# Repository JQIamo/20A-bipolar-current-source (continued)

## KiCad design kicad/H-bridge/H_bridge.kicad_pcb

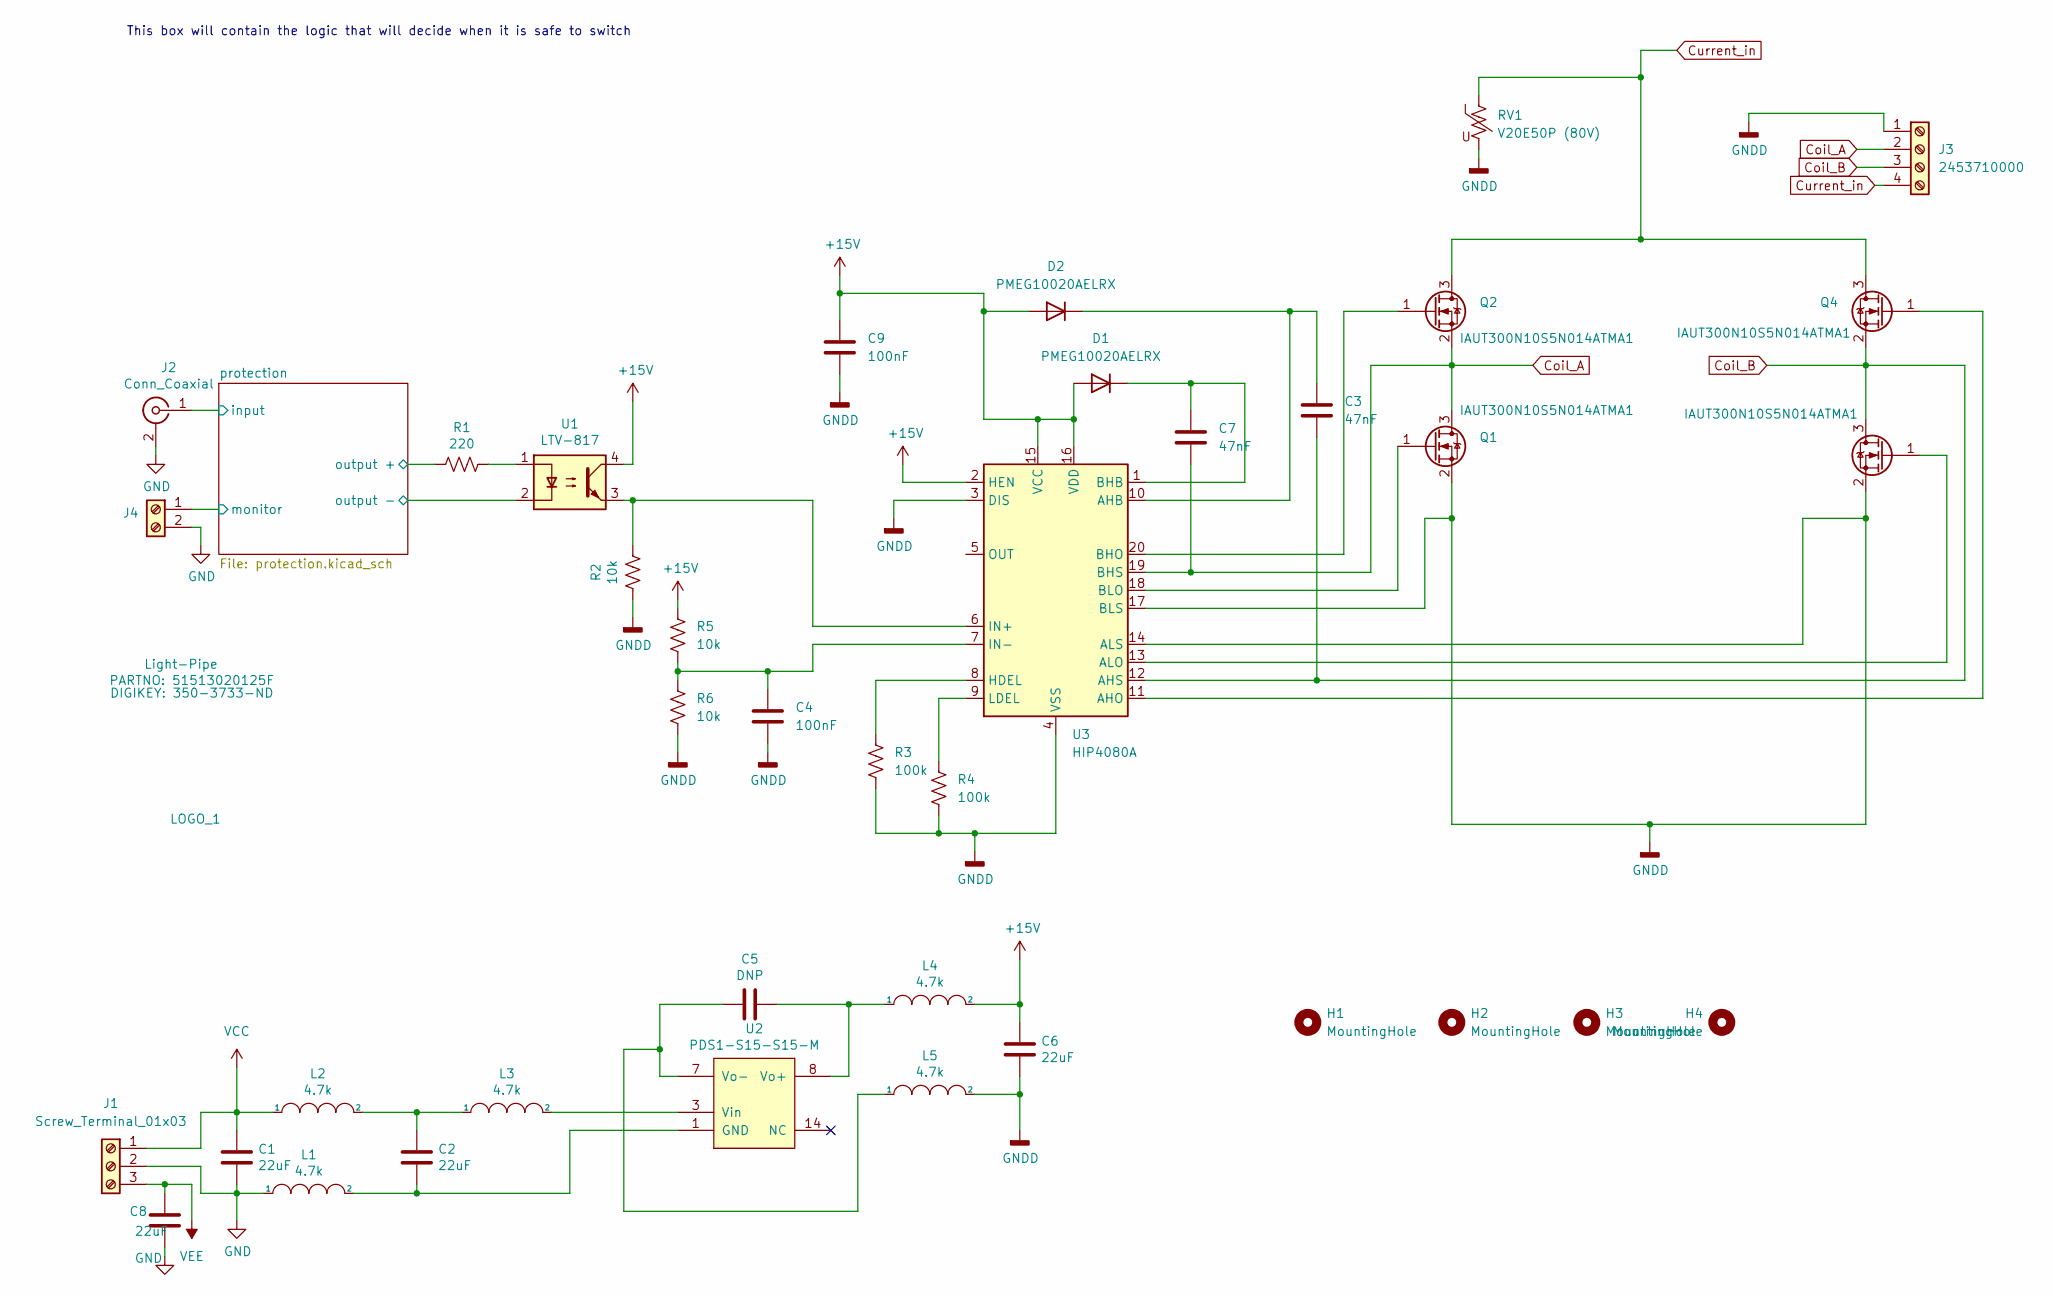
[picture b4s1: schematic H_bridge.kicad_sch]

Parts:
BOM1: Light-Pipe; PARTNO 51513020125F; DIGIKEY 350-3733-ND
C1, C2, C6, C8: 22uF; C_0805_2012Metric; PARTNO C2012X5R1V226M125AC; DIGIKEY 445-14428-1-ND
C3, C7: 47nF; C_0805_2012Metric; PARTNO C0805C473K2RECAUTO; DIGIKEY 399-C0805C473K2RECAUTOCT-ND
C4, C9: 100nF; C_0805_2012Metric; PARTNO CC0805KRX7R9BB104; DIGIKEY 311-1140-1-ND
C5: DNP; C_0805_2012Metric
D1, D2: PMEG10020AELRX; Nexperia_CFP3_SOD-123W; PARTNO PMEG10020AELRX; DIGIKEY 1727-2283-1-ND
H1, H2, H3, H4: MountingHole; MountingHole_3.5mm
J1: Screw_Terminal_01x03; TerminalBlock_4Ucon_1x03_P3.50mm_Horizontal; PARTNO 1984620; DIGIKEY 277-1722-ND
J2: Conn_Coaxial; BNC_Socket_TYCO-AMP; PARTNO 5227161-7; DIGIKEY A32260-ND
J3: 2453710000; CONN_2453710000; PARTNO 2453710000; DIGIKEY 2453710000-ND
J4: Screw_Terminal_01x02; TerminalBlock_4Ucon_1x02_P3.50mm_Horizontal; PARTNO 1984617; DIGIKEY 277-1721-ND
L1, L2, L3, L4, L5: 4.7k; L_0805; PARTNO BLM21HE472SN1L; DIGIKEY 490-BLM21HE472SN1LCT-ND
LOGO_1: JQI-Logo
Q1, Q2, Q3, Q4: IAUT300N10S5N014ATMA1; Infineon_PG-HSOF-8-1_ThermalVias; PARTNO IAUT300N10S5N014ATMA1; DIGIKEY 448-IAUT300N10S5N014ATMA1CT-ND
R1: 220; R_0805; PARTNO CRGCQ0805F220R; DIGIKEY A129741CT-ND
R2, R5, R6: 10k; R_0805_2012Metric; PARTNO CRGCQ0805F10K; DIGIKEY A129761CT-ND
R3, R4: 100k; R_0805_2012Metric; PARTNO CRG0805F100K; DIGIKEY A106052CT-ND
RV1: V20E50P (80V); RV_Disc_D15.5mm_W7.5mm_P7.5mm; PARTNO V20E50P; DIGIKEY F6901-ND
U1: LTV-817; DIP-4_W10.16mm_LongPads; PARTNO LTV-817; DIGIKEY 160-1366-5-ND
U2: PDS1-S15-S15-M; DCDC-Conv_muRata_NXE2SxxxxMC; PARTNO PDS1-S15-S15-M; DIGIKEY 102-4546-ND
U3: HIP4080A; SO-20_12.8x7.5mm_P1.27mm; PARTNO HIP4080AIBZT; DIGIKEY HIP4080AIBZTCT-ND

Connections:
+15V: C6.2, C9.1, D1.2 (A), D2.2 (A), L4.2, R5.1, U1.4, U3.2 (HEN), U3.15 (VCC), U3.16 (VDD)
/protection/input: J2.1 (In); also elsewhere on the board
/protection/monitor: J4.1; also elsewhere on the board
/protection/output +: R1.2; also elsewhere on the board
/protection/output -: U1.2; also elsewhere on the board
Coil_A: C7.2, J3.2, Q1.3 (D), Q2.2 (S), U3.19 (BHS)
Coil_B: C3.2, J3.3, Q3.3 (D), Q4.2 (S), U3.12 (AHS)
Current_in: J3.4, Q2.3 (D), Q4.3 (D), RV1.1
GND: C1.2, C8.2, J1.2, J2.2 (Ext), J4.2, L1.1; also elsewhere on the board
GNDD: C4.2, C6.1, C9.2, J3.1, L5.2, Q1.2 (S), Q3.2 (S), R2.2, R3.2, R4.2, R6.2, RV1.2, U3.3 (DIS), U3.4 (VSS), U3.14 (ALS), U3.17 (BLS)
unnamed: C2.1, L2.2, L3.1
unnamed: C7.1, D1.1 (K), U3.1 (BHB)
unnamed: C3.1, D2.1 (K), U3.10 (AHB)
unnamed: Q1.1 (G), U3.18 (BLO)
unnamed: Q2.1 (G), U3.20 (BHO)
unnamed: Q3.1 (G), U3.13 (ALO)
unnamed: Q4.1 (G), U3.11 (AHO)
unnamed: R1.1, U1.1
unnamed: C2.2, L1.2, U2.1 (GND)
unnamed: L3.2, U2.3 (Vin)
unnamed: C5.1, L4.1, U2.8 (Vo+)
unnamed: C5.2, L5.1, U2.7 (Vo-)
unnamed: R3.1, U3.8 (HDEL)
unnamed: R2.1, U1.3, U3.6 (IN+)
unnamed: C4.1, R5.2, R6.1, U3.7 (IN-)
unnamed: R4.1, U3.9 (LDEL)
VCC: C1.1, J1.1, L2.1; also elsewhere on the board
VEE: C8.1, J1.3; also elsewhere on the board

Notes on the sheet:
This box will contain the logic that will decide when it is safe to switch

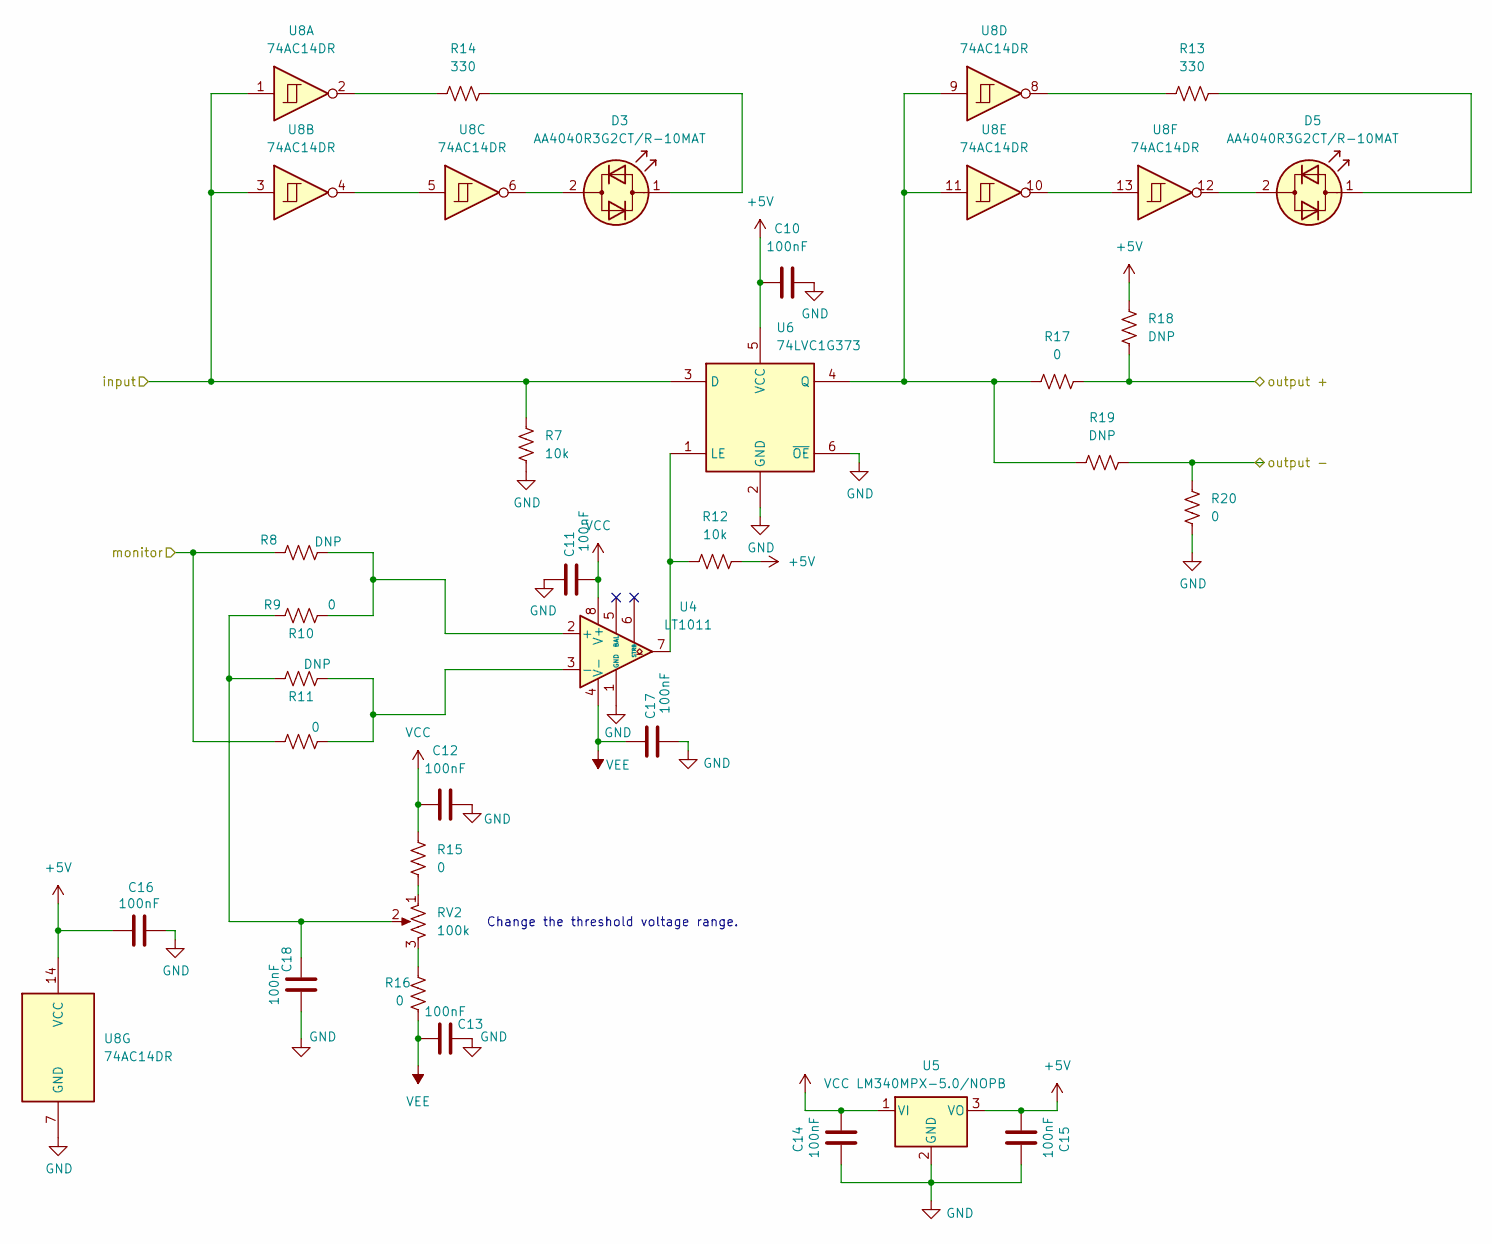
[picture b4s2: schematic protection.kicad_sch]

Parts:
C10, C11, C12, C13, C14, C15, C16, C17, C18: 100nF; C_0805_2012Metric; PARTNO CC0805KRX7R9BB104; DIGIKEY 311-1140-1-ND
D3, D5: AA4040R3G2CT/R-10MAT; LED_boomerang; PARTNO AA4040R3G2CT/R-10MAT; DIGIKEY 754-AA4040R3G2CT/R-10MATCT-ND
R7, R12: 10k; R_0805_2012Metric; PARTNO CRGCQ0805F10K; DIGIKEY A129761CT-ND
R8, R10, R18, R19: DNP; R_0805_2012Metric
R9, R11, R15, R16, R17, R20: 0; R_0805_2012Metric; PARTNO CRG0805ZR; DIGIKEY A106066CT-ND
R13, R14: 330; R_0805_2012Metric; PARTNO CRGCQ0805F330R; DIGIKEY A129743CT-ND
RV2: 100k; Potentiometer_Bourns_3266Y_Vertical; PARTNO 3266Y-1-104LF; DIGIKEY 3266Y-1-104LF-ND
U4: LT1011; SO-8_3.9x4.9mm_P1.27mm; PARTNO LT1011CS8#PBF; DIGIKEY LT1011CS8#PBF-ND
U5: LM340MPX-5.0/NOPB; SOT-223-3_TabPin2; PARTNO LM340MPX-5.0/NOPB; DIGIKEY LM340MPX-5.0/NOPBCT-ND
U6: 74LVC1G373; SOT-363_SC-70-6; PARTNO SN74LVC1G373DCKR; DIGIKEY 296-18775-1-ND
U8: 74AC14DR; SOIC-14_3.9x8.7mm_P1.27mm; PARTNO SN74AC14DR; DIGIKEY 296-4300-1-ND

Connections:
+5V: C10.1, C15.2, C16.2, R12.2, R18.2, U5.3 (VO), U6.5 (VCC), U8.14 (VCC)
/protection/input: R7.1, U6.3 (D), U8.1, U8.3; also elsewhere on the board
/protection/monitor: R8.1, R11.1; also elsewhere on the board
/protection/output +: R17.2, R18.1; also elsewhere on the board
/protection/output -: R19.1, R20.2; also elsewhere on the board
GND: C10.2, C11.2, C12.2, C13.2, C14.1, C15.1, C16.1, C17.1, C18.1, R7.2, R20.1, U4.1 (GND), U5.2 (GND), U6.2 (GND), U6.6 (~OE), U8.7 (GND); also elsewhere on the board
unnamed: C18.2, R9.1, R10.1, RV2.2
unnamed: D3.2 (AK), U8.6
unnamed: D3.1 (KA), R14.2
unnamed: D5.2 (AK), U8.12
unnamed: D5.1 (KA), R13.2
unnamed: R13.1, U8.8
unnamed: R14.1, U8.2
unnamed: R15.1, RV2.1
unnamed: R16.2, RV2.3
unnamed: R8.2, R9.2, U4.2 (+)
unnamed: R10.2, R11.2, U4.3 (-)
unnamed: R12.1, U4.7, U6.1 (LE)
unnamed: R17.1, R19.2, U6.4 (Q), U8.9, U8.11
unnamed: U8.4, U8.5
unnamed: U8.10, U8.13
VCC: C11.1, C12.1, C14.2, R15.2, U4.8 (V+), U5.1 (VI); also elsewhere on the board
VEE: C13.1, C17.2, R16.1, U4.4 (V-); also elsewhere on the board

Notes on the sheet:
Change the threshold voltage range.

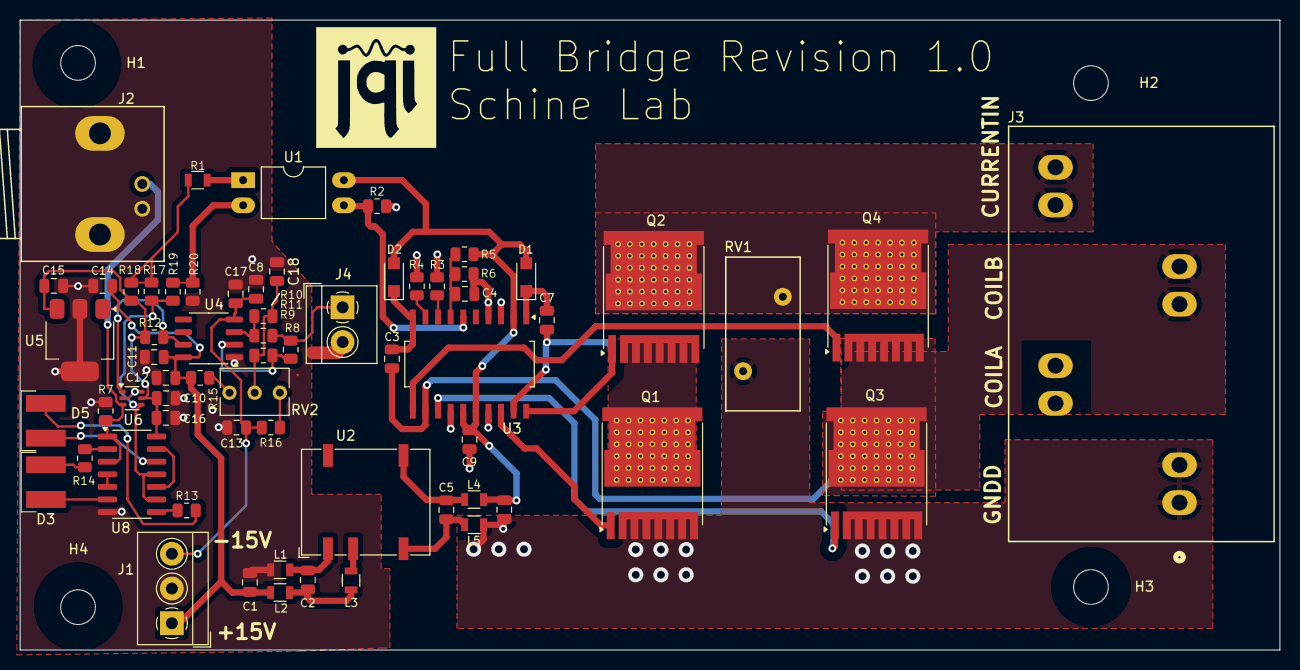
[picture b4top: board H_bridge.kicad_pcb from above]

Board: 2 copper layers, 127.0 x 63.5 mm, 69 parts (0 on the bottom side), 44 nets.

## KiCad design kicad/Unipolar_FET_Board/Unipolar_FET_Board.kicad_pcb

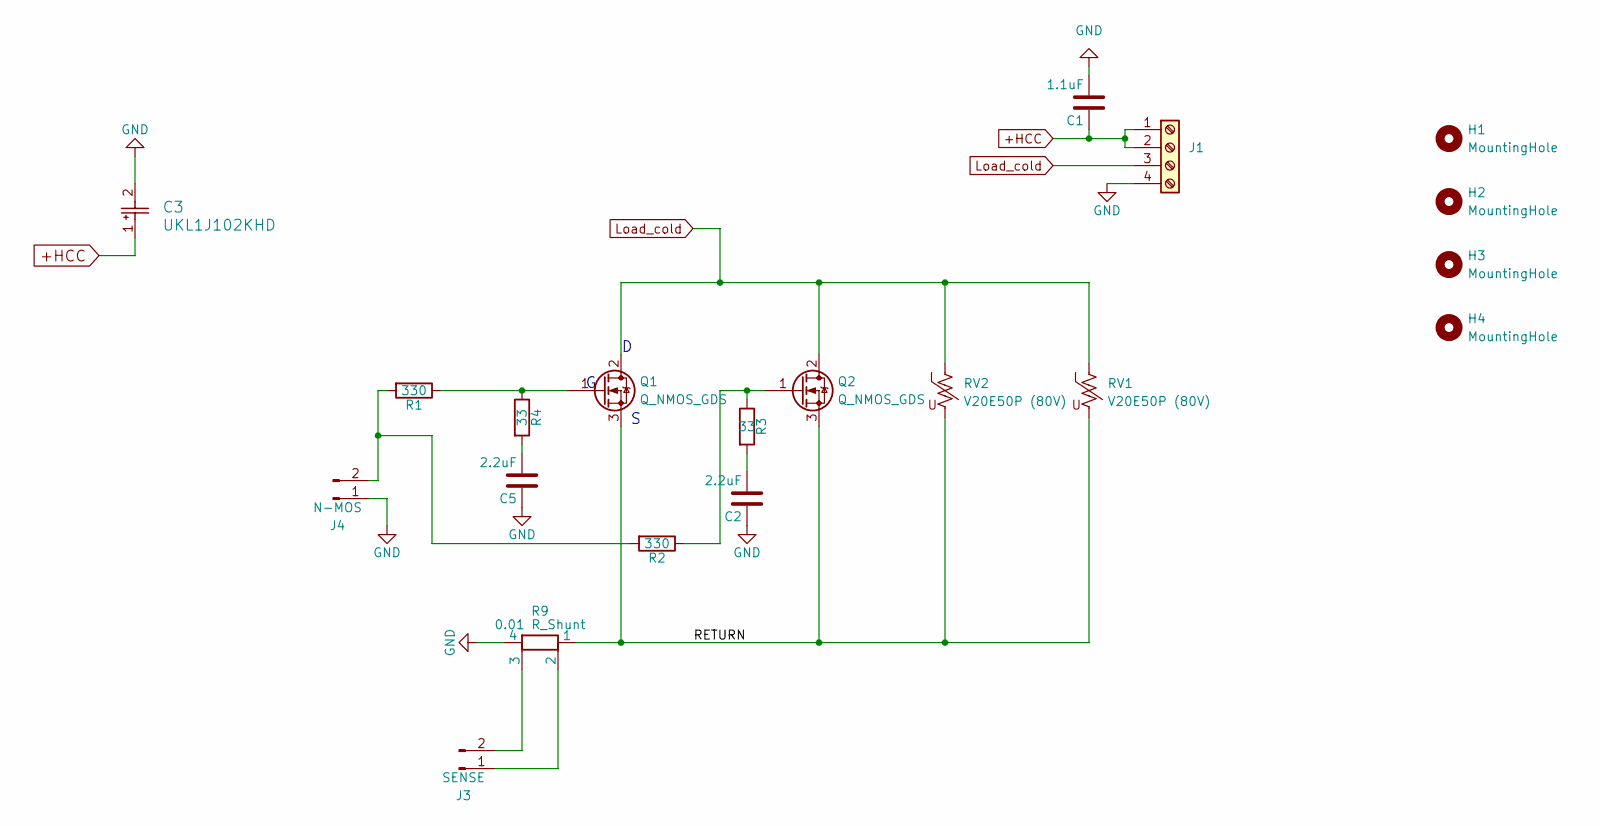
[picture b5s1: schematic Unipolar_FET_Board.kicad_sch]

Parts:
C1: 1.1uF; C_0603_1608Metric; MPN C0603C104J5RACAUTO; DIGIKEY PARTNO 399-6853-1-ND
C2, C5: 2.2uF; C_0603_1608Metric; MPN C0603C104J5RACAUTO; DIGIKEY PARTNO 399-6853-1-ND
C3: UKL1J102KHD; CP_Radial_D18.0mm_P7.50mm; PARTNO UKL1J102KHD; DIGIKEY 493-16867-ND
H1, H2, H3, H4: MountingHole; MountingHole_4mm
J1: Screw_Terminal_01x04; CONN_2453710000; PARTNO 2453710000; DIGIKEY 2453710000-ND
J3: SENSE; PinHeader_1x02_P2.54mm_Vertical
J4: N-MOS; PinHeader_1x02_P2.54mm_Vertical
Q1, Q2: Q_NMOS_GDS; PowerMOS; PARTNO IXFN520N075T2; DIGIKEY IXFN520N075T2-ND
R1, R2: 330; R_0603_1608Metric_Pad0.98x0.95mm_HandSolder; DIGIKEY PARTNO P20.00BYCT-ND
R3, R4: 33; R_0603_1608Metric_Pad0.98x0.95mm_HandSolder; DIGIKEY PARTNO P20.00BYCT-ND
R9: 0.01 R_Shunt; SIP-4-ShuntResistor-Riedon; PARTNO PCS-0R01D1; DIGIKEY 696-PCS-0R01D1-ND
RV1, RV2: V20E50P (80V); RV_Disc_D15.5mm_W7.5mm_P7.5mm; PARTNO V20E50P; DIGIKEY F6901-ND

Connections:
+HCC: C1.1, C3.1, J1.1, J1.2
/RETURN: Q1.3 (S), Q2.3 (S), R9.1, RV1.2, RV2.2
GND: C1.2, C2.1, C3.2, C5.1, J1.4, J4.1, R9.4
Load_cold: J1.3, Q1.2 (D), Q2.2 (D), RV1.1, RV2.1
unnamed: C2.2, R3.2
unnamed: C5.2, R4.2
unnamed: J3.1, R9.2
unnamed: J3.2, R9.3
unnamed: J4.2, R1.2, R2.2
unnamed: Q1.1 (G), R1.1, R4.1
unnamed: Q2.1 (G), R2.1, R3.1

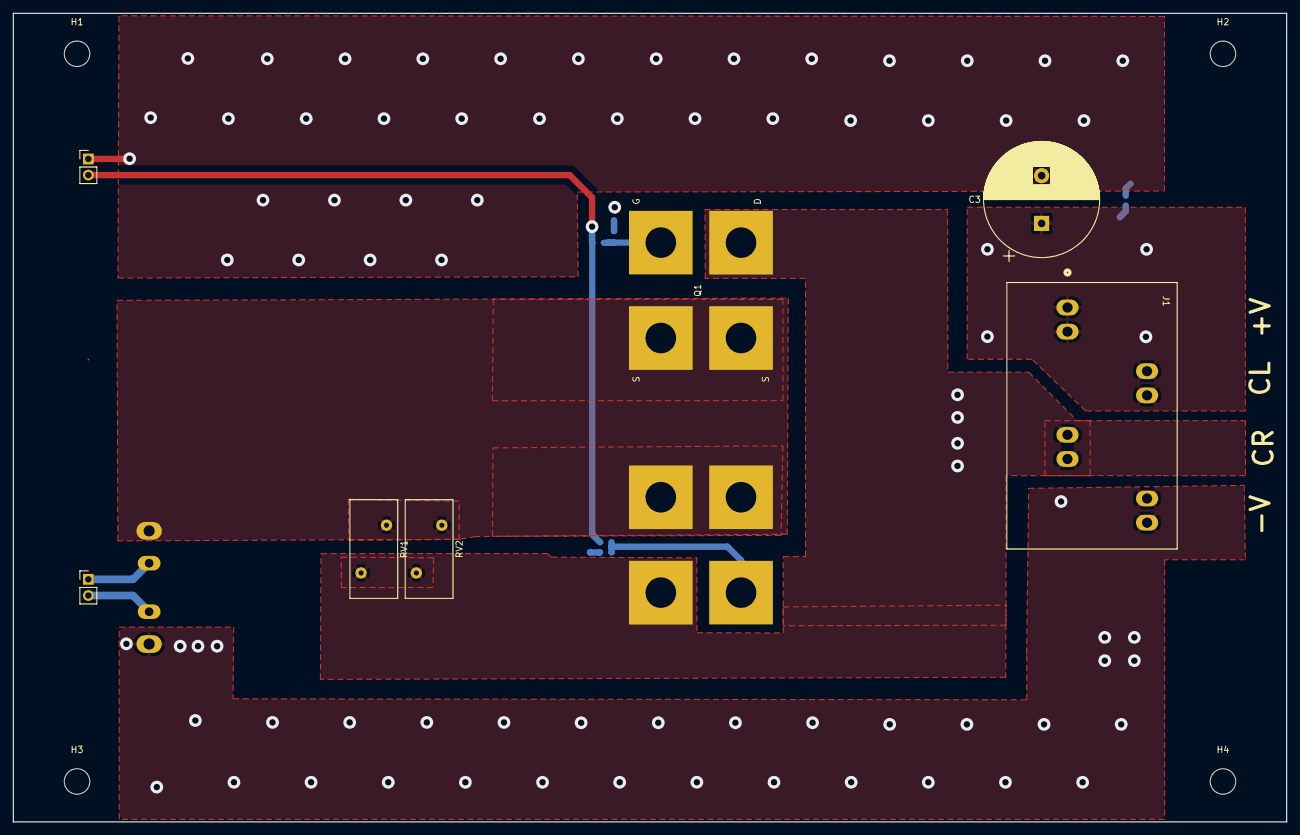
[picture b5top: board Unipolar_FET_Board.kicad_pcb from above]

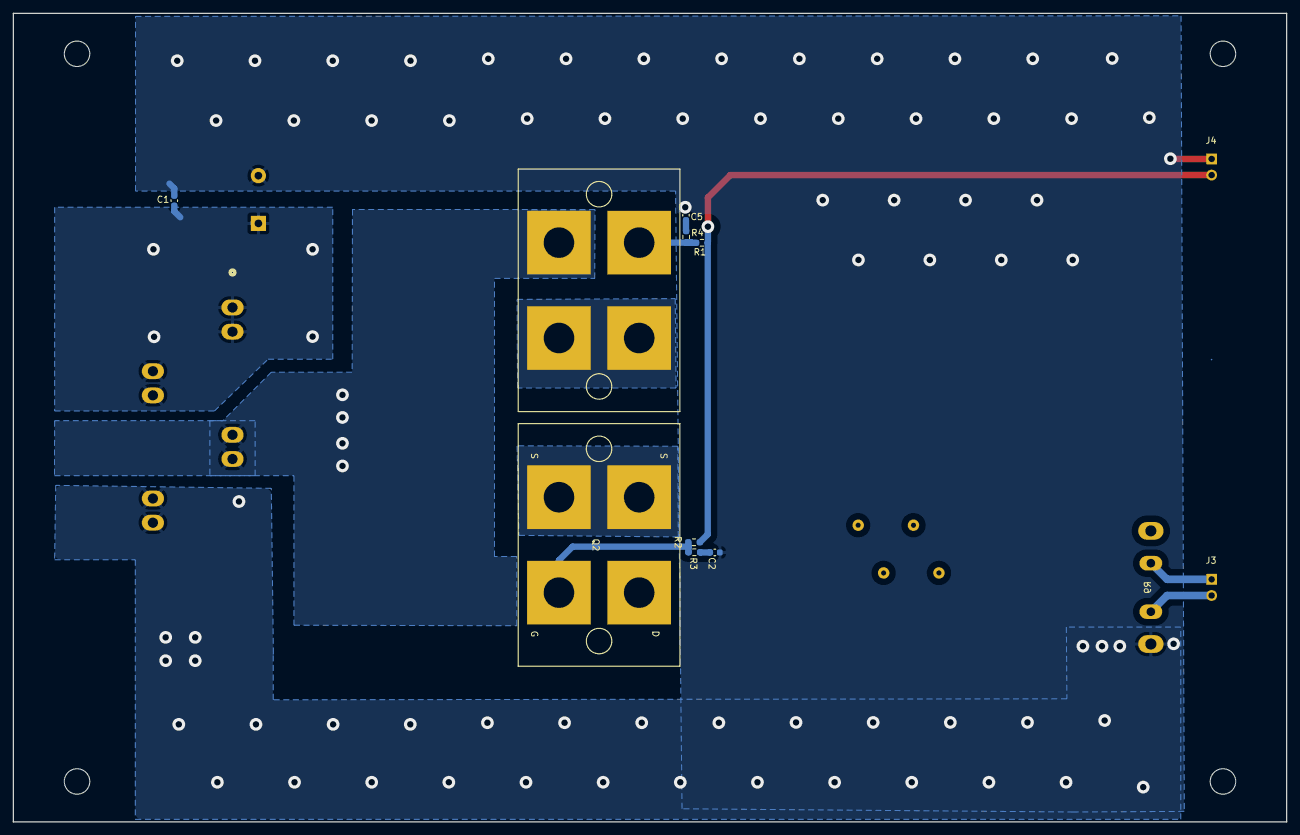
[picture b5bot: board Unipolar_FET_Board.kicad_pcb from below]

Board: 2 copper layers, 200.0 x 127.0 mm, 20 parts (9 on the bottom side), 11 nets.

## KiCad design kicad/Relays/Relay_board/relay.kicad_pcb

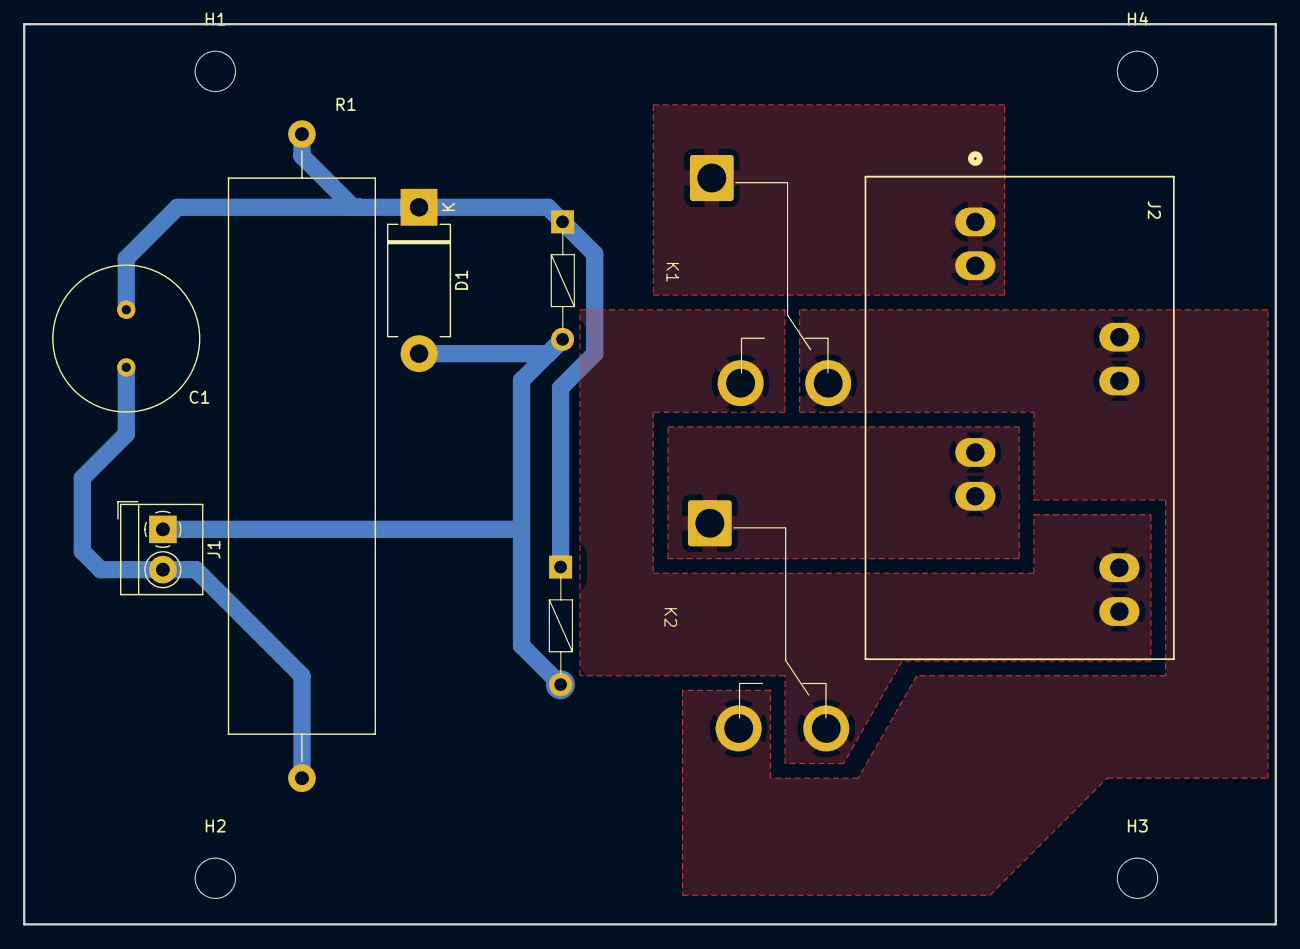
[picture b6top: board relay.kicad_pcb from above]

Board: 2 copper layers, 108.6 x 78.1 mm, 11 parts (0 on the bottom side), 7 nets.

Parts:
C1: 100uF; C_Radial_D12.5mm_H25.0mm_P5.00mm
D1: D; D_DO-201AD_P12.70mm_Horizontal
H1, H2, H3, H4: MountingHole; MountingHole_3.5mm
J1: Screw_Terminal_01x02; TerminalBlock_4Ucon_1x02_P3.50mm_Horizontal
J2: Screw_Terminal_01x04; CONN_2453710000
K1, K2: J115F11CH24VDCS61.5U; SPDT-Relay-[J115F11CH24VDCS61.5U]
R1: 470; R_Axial_Power_L48.0mm_W12.5mm_P55.88mm

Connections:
/ENERGIZE: C1.2, J1.2, R1.2
CoilA: J2.3, K2.11
CoilB: J2.1, K1.11
Current In: J2.4, K1.12, K2.14
GND: D1.2 (A), J1.1, K1.A1, K2.A1
GNDD: J2.2, K1.14, K2.12
unnamed: C1.1, D1.1 (K), K1.A2, K2.A2, R1.1

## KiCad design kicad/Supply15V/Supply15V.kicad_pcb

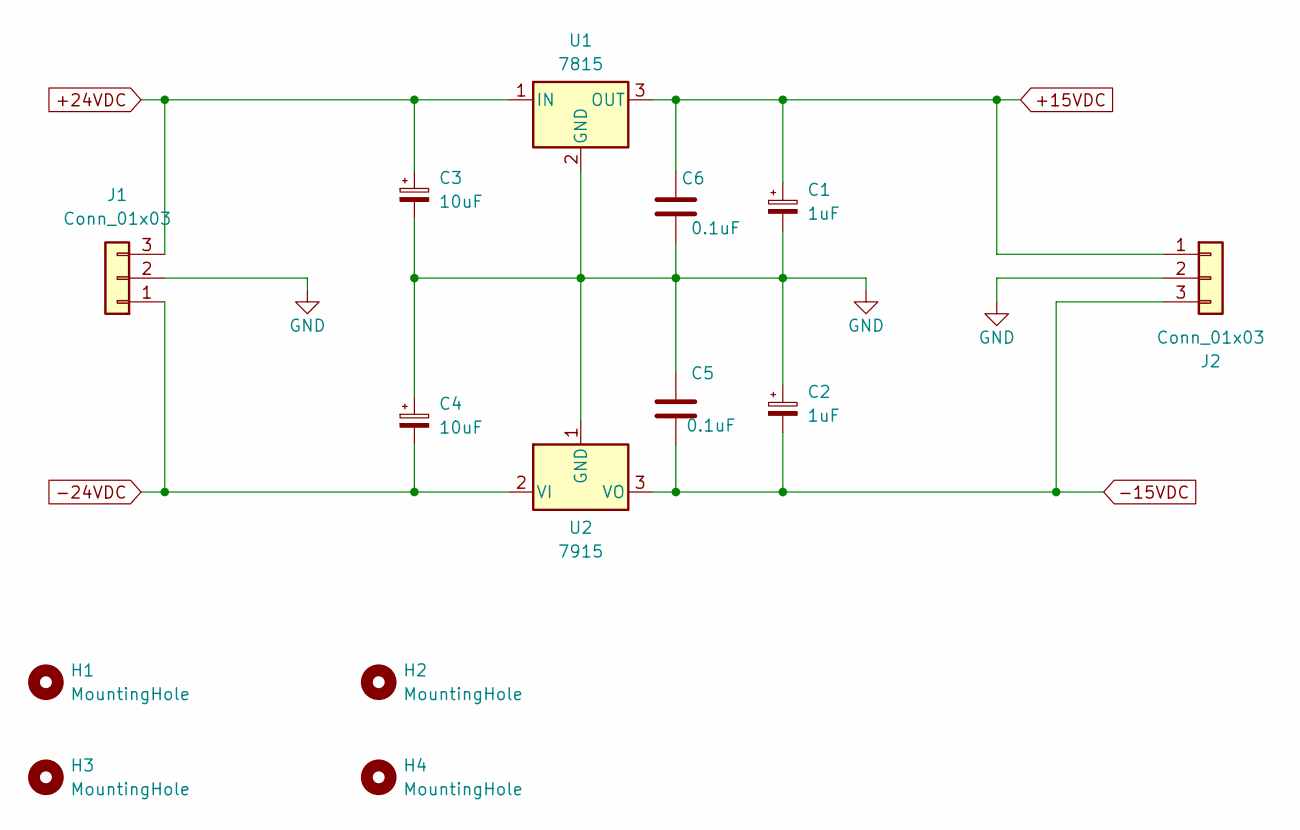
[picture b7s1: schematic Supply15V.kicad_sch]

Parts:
C1, C2: 1uF; CP_Radial_Tantal_D4.5mm_P2.50mm; MPN EEE-FK1H221P; DIGIKEY PARTNO PCE3812CT-ND
C3, C4: 10uF; CP_Radial_D5.0mm_P2.50mm; MPN EEE-FK1H221P; DIGIKEY PARTNO PCE3812CT-ND
C5, C6: 0.1uF; C_Disc_D4.3mm_W1.9mm_P5.00mm
H1, H2, H3, H4: MountingHole; MountingHole_4.3mm_M4_ISO7380
J1, J2: Conn_01x03; TerminalBlock_4Ucon_1x03_P3.50mm_Horizontal
U1: 7815; TO-220-3_Vertical
U2: 7915; TO-220-3_Vertical

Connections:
+15VDC: C1.1, C6.2, J2.1, U1.3 (OUT)
+24VDC: C3.1, J1.3, U1.1 (IN)
-15VDC: C2.2, C5.1, J2.3, U2.3 (VO)
-24VDC: C4.2, J1.1, U2.2 (VI)
GND: C1.2, C2.1, C3.2, C4.1, C5.2, C6.1, J1.2, J2.2, U1.2 (GND), U2.1 (GND)

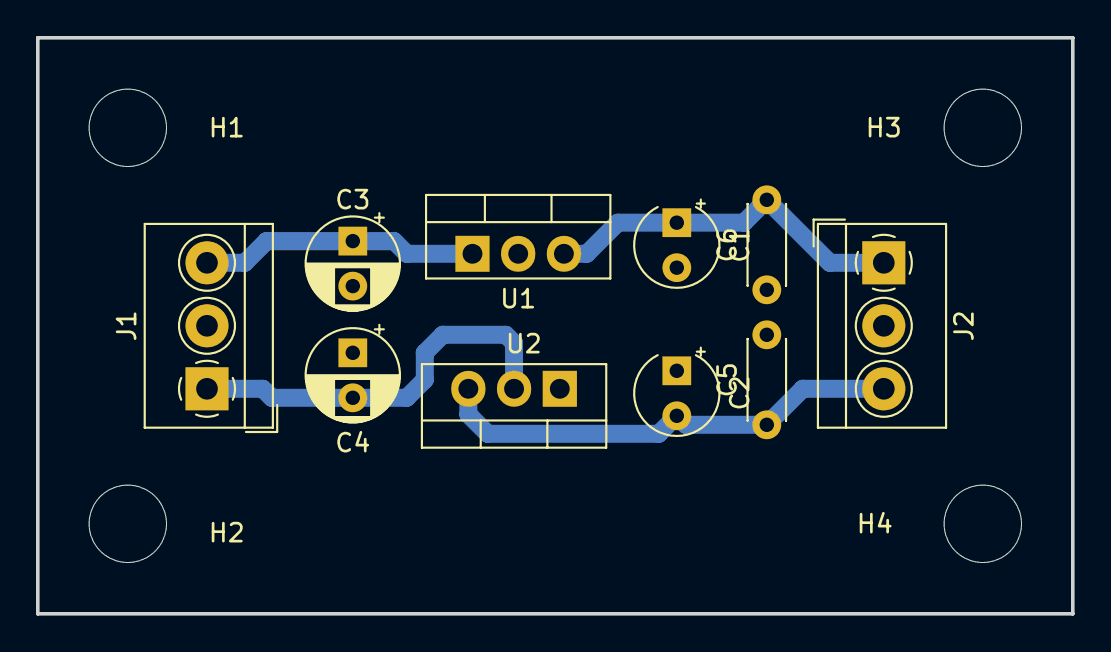
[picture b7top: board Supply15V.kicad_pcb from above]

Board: 2 copper layers, 57.5 x 32.0 mm, 14 parts (0 on the bottom side), 5 nets.

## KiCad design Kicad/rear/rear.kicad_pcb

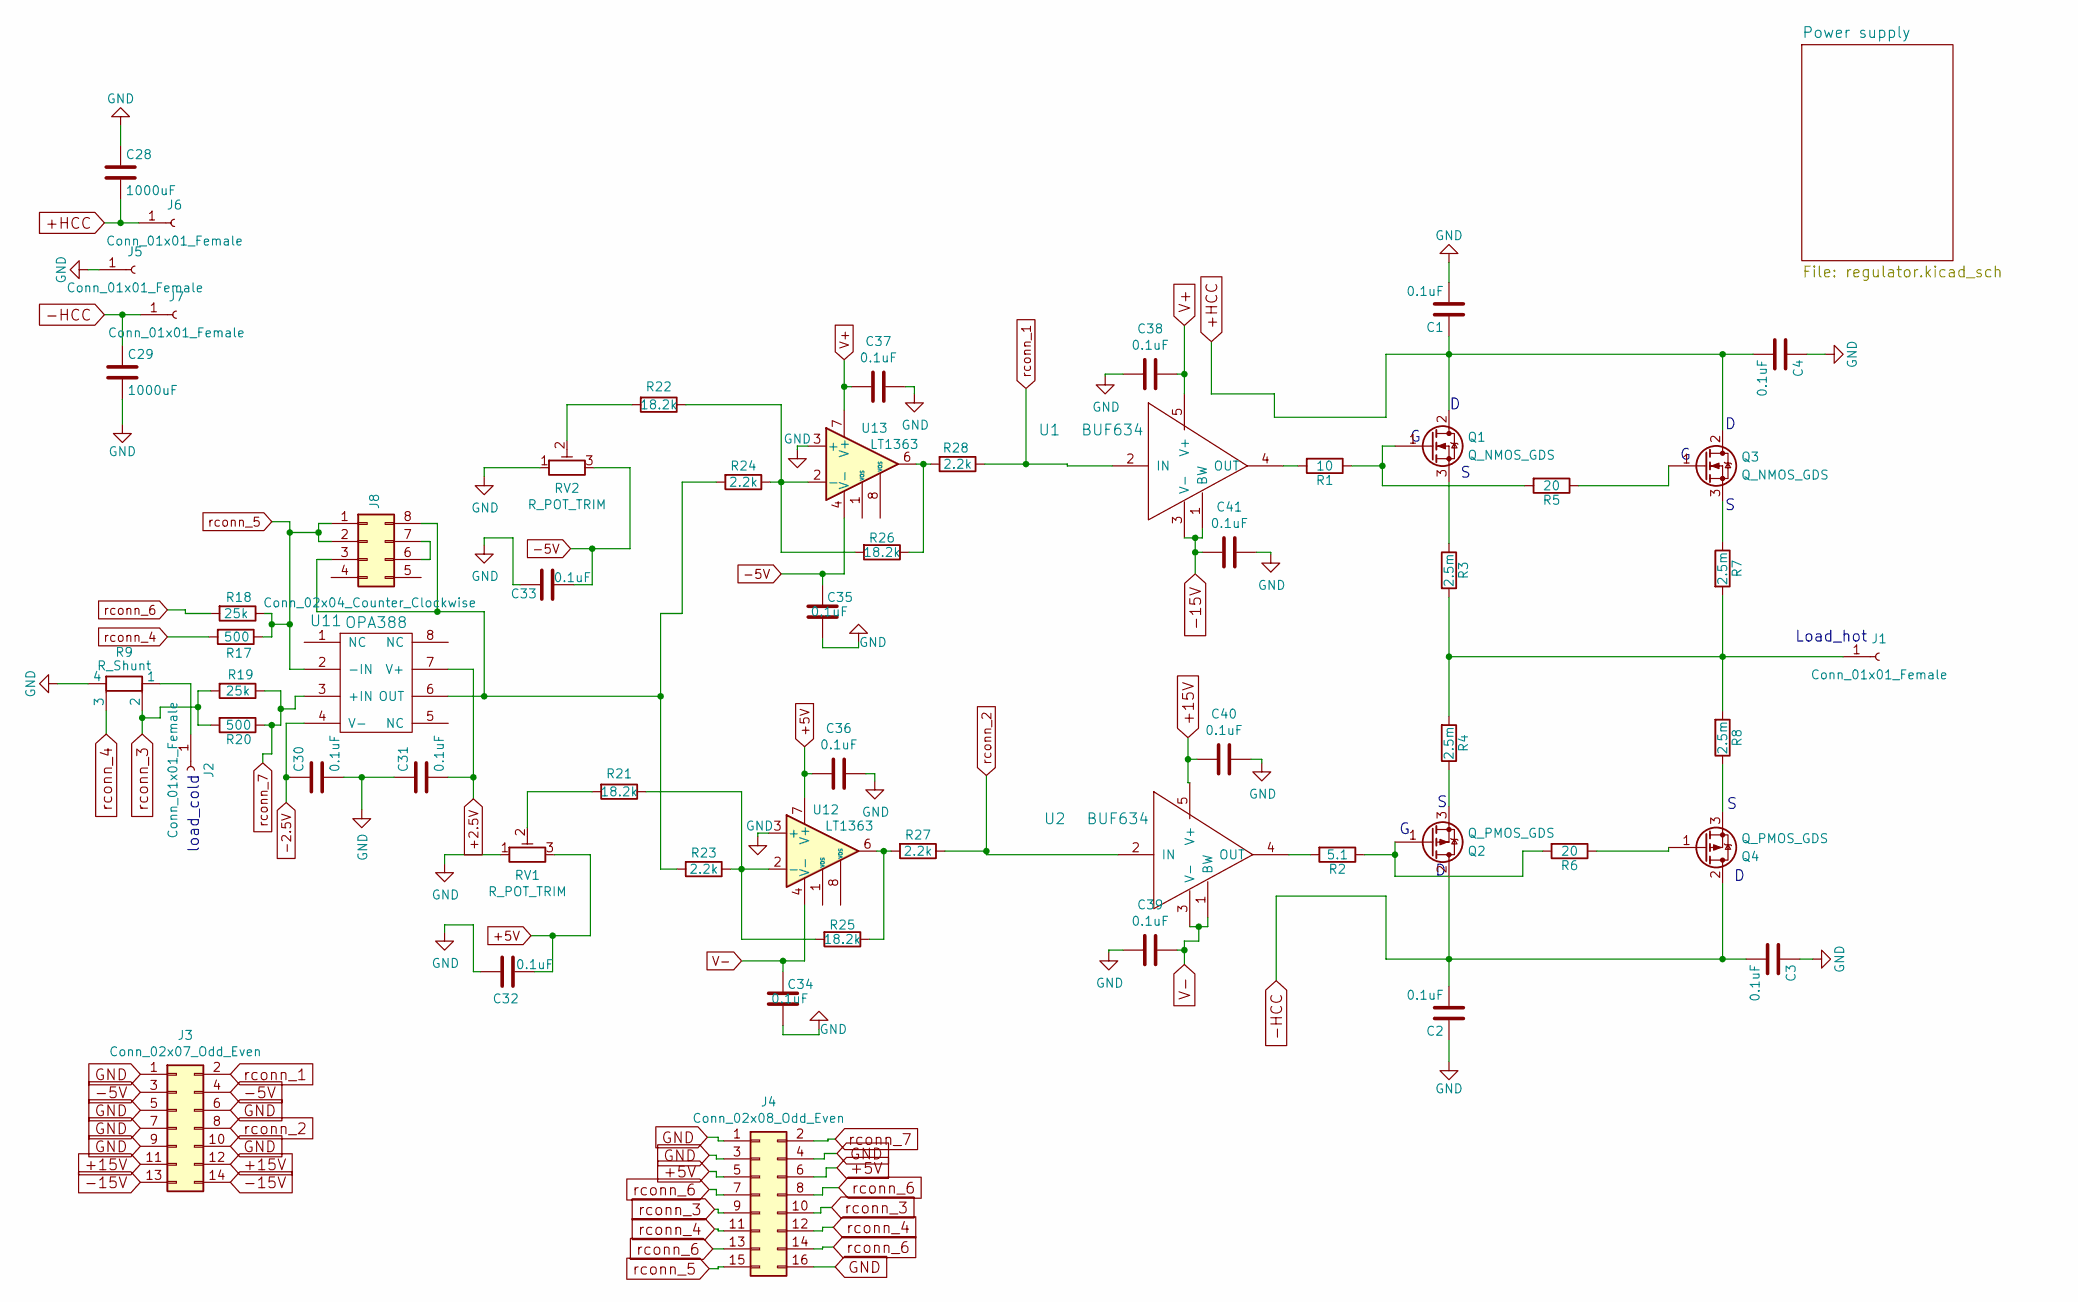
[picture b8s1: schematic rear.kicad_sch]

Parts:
C1, C2, C3, C4, C30, C31, C32, C33, C34, C35, C36, C37, C38, C39, C40, C41: 0.1uF; C_0603; MPN C0603C104J5RACAUTO; DIGIKEY PARTNO 399-6853-1-ND
C28, C29: 1000uF; CAPCITOR_TOT; DIGIKEY PARTNO 647-UKL1J102KHD
J1, J2, J5, J6, J7: Conn_01x01_Female; SAFETY-BANANA-JACK-CT3151
J3: Conn_02x07_Odd_Even; 14PinConn; MPN 302-S141/ AWP 14-8240-T; DIGIKEY PARTNO ED10522-ND/ HHSC14H-ND
J4: Conn_02x08_Odd_Even; 16PinConn; MPN 302-S161/ AWP 16-8240-T; DIGIKEY PARTNO ED10523-ND/ HHSC16H-ND
J8: Conn_02x04_Counter_Clockwise; Socket_Strip_Straight_2x04_Pitch2.54mm_SMD; DIGIKEY PARTNO 437-1148730841134161
Q1, Q3: Q_NMOS_GDS; PowerMOS; DIGIKEY PARTNO IXFN520N075T2-ND
Q2, Q4: Q_PMOS_GDS; PowerMOS; DIGIKEY PARTNO IXTN170P10P-ND
R1: 10; R_0603; DIGIKEY PARTNO P10.00BYCT-ND
R2: 5.1; R_0603; DIGIKEY PARTNO P5.1BZCT-ND
R3, R4, R7, R8: 2.5m; R_2512; DIGIKEY PARTNO A129569CT-ND
R5, R6: 20; R_0603; DIGIKEY PARTNO P20.00BYCT-ND
R9: R_Shunt; SHR4-3825
R17, R20: 500; R_0805; DIGIKEY PARTNO 804-1216-ND
R18, R19: 25k; R_2512; DIGIKEY PARTNO 804-1122-6-ND
R21, R22, R25, R26: 18.2k; R_0805; DIGIKEY PARTNO RNCP0805FTD18K2CT-ND
R23, R24, R27, R28: 2.2k; R_0805; DIGIKEY PARTNO 749-1728-1-ND
RV1, RV2: R_POT_TRIM; Potentiometer_Trimmer_Bourns_3214W; DIGIKEY PARTNO 3214W-102EDKR-ND
U1, U2: BUF634; TO-263-5_TabPin6; DIGIKEY PARTNO 296-25929-1-ND
U11: OPA388; SOIC-8_3.9x4.9mm_Pitch1.27mm; DIGIKEY PARTNO 296-45348-1-ND
U12, U13: LT1363; SOIC-8_3.9x4.9mm_Pitch1.27mm; DIGIKEY PARTNO LT1363CS8#TRPBFCT-ND

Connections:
+2.5V: C31.2, U11.7 (V+); also elsewhere on the board
+5V: C32.1, C36.2, J4.5, J4.6, RV1.3, U12.7 (V+); also elsewhere on the board
+15V: C40.2, J3.11, J3.12, U2.5 (V+); also elsewhere on the board
+HCC: C1.1, C4.2, C28.2, J6.1, Q1.2 (D), Q3.2 (D)
-2.5V: C30.1, U11.4 (V-); also elsewhere on the board
-5V: C33.1, C35.2, J3.3, J3.4, RV2.3, U13.4 (V-); also elsewhere on the board
-15V: C41.2, J3.13, J3.14, U1.1 (BW), U1.3 (V-); also elsewhere on the board
-HCC: C2.2, C3.2, C29.1, J7.1, Q2.2 (D), Q4.2 (D)
GND: C1.2, C2.1, C3.1, C4.1, C28.1, C29.2, C30.2, C31.1, C32.2, C33.2, C34.1, C35.1, C36.1, C37.1, C38.2, C39.2, C40.1, C41.1, J3.1, J3.5, J3.6, J3.7, J3.9, J3.10, J4.1, J4.3, J4.4, J4.16, J5.1, R9.4, RV1.1, RV2.1, U12.3 (+), U13.3 (+); also elsewhere on the board
unnamed: J1.1, R3.2, R4.2, R7.2, R8.2
unnamed: J2.1, R9.1
unnamed: J8.3, J8.8, R23.2, R24.2, U11.6 (OUT)
unnamed: J8.6, J8.7
unnamed: Q1.1 (G), R1.1, R5.2
unnamed: Q1.3 (S), R3.1
unnamed: Q2.1 (G), R2.1, R6.2
unnamed: Q2.3 (S), R4.1
unnamed: Q3.1 (G), R5.1
unnamed: Q3.3 (S), R7.1
unnamed: Q4.1 (G), R6.1
unnamed: Q4.3 (S), R8.1
unnamed: R1.2, U1.4 (OUT)
unnamed: R2.2, U2.4 (OUT)
unnamed: R21.1, R23.1, R25.2, U12.2 (-)
unnamed: R21.2, RV1.2
unnamed: R22.1, R24.1, R26.2, U13.2 (-)
unnamed: R22.2, RV2.2
unnamed: R25.1, R27.2, U12.6
unnamed: R26.1, R28.2, U13.6
V+: C37.2, C38.1, U1.5 (V+), U13.7 (V+); also elsewhere on the board
V-: C34.2, C39.1, U2.1 (BW), U2.3 (V-), U12.4 (V-); also elsewhere on the board
rconn_1: J3.2, R28.1, U1.2 (IN)
rconn_2: J3.8, R27.1, U2.2 (IN)
rconn_3: J4.9, J4.10, R9.2, R19.2, R20.2
rconn_4: J4.11, J4.12, R9.3, R17.2
rconn_5: J4.15, J8.1, J8.2, R17.1, R18.1, U11.2 (-IN)
rconn_6: J4.7, J4.8, J4.13, J4.14, R18.2
rconn_7: J4.2, R19.1, R20.1, U11.3 (+IN)

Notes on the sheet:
load_cold
Load_hot
